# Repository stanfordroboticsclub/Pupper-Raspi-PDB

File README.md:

# Pupper Power Distribution Board for Raspberry Pi
This is a custom power distribution board for the versions of Pupper that generate PWM signals from the Raspberry Pi. 

Don't know what Pupper is? It's a cheap dynamics quadruped robot that you can build at home.
- Check out the [Project Page](https://stanfordstudentrobotics.org/pupper)
- Check out the [Code](https://github.com/stanfordroboticsclub/stanfordquadruped)

## Fabrication
1. Upload Gerbers.zip (in this directory) to the quoting mechanism on jlcpcb.com
2. It'll then give you some options on how you want the pcb made
3. Make sure you specify 2oz copper to support the high current from the servos.
4. You can leave everything else as default!

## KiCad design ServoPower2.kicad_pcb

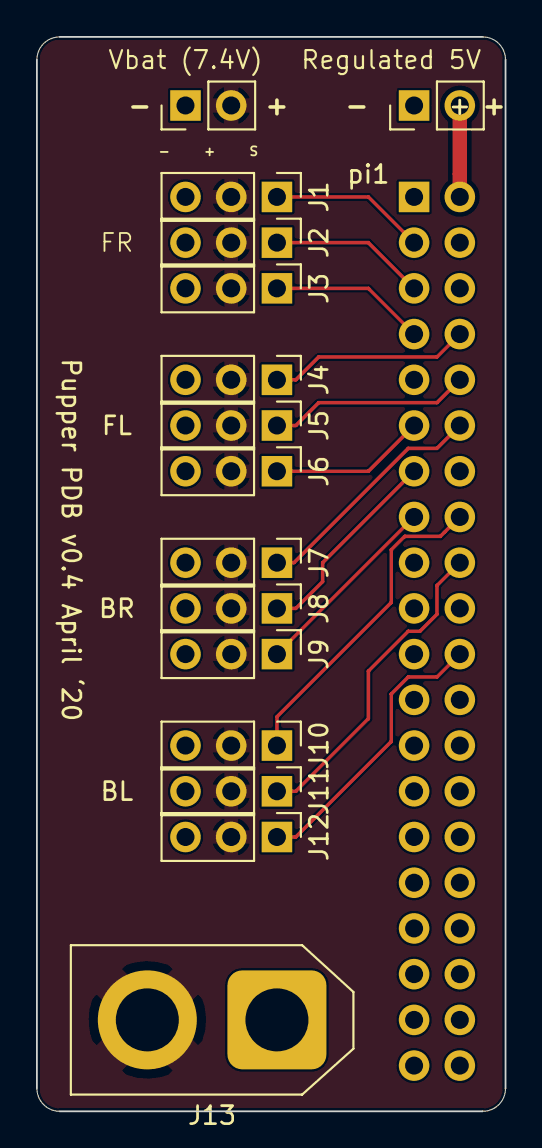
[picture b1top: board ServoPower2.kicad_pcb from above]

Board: 2 copper layers, 26.0 x 59.7 mm, 16 parts (1 on the bottom side), 15 nets.

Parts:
J1, J2, J3, J4, J5, J6, J7, J8, J9, J10, J11, J12: Conn_01x03; PinHeader_1x03_P2.54mm_Vertical
J13: Conn_01x02; AMASS_XT60-M_1x02_P7.20mm_Vertical
J14, J15: Conn_01x02; PinHeader_1x02_P2.54mm_Vertical
pi1: pi; PinSocket_2x20_P2.54mm_Vertical

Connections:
+5V: J15.2, pi1.2
/S11: J1.1, pi1.3
/S12: J2.1, pi1.5
/S13: J3.1, pi1.7
/S21: J4.1, pi1.8
/S22: J5.1, pi1.10
/S23: J6.1, pi1.11
/S31: J7.1, pi1.12
/S32: J8.1, pi1.13
/S33: J9.1, pi1.15
/S41: J10.1, pi1.16
/S42: J11.1, pi1.18
/S43: J12.1, pi1.22
GND: J1.3, J2.3, J3.3, J4.3, J5.3, J6.3, J7.3, J8.3, J9.3, J10.3, J11.3, J12.3, J13.1, J14.1, J15.1, pi1.6, pi1.9, pi1.14, pi1.20, pi1.25, pi1.30, pi1.34, pi1.39
VDD: J1.2, J2.2, J3.2, J4.2, J5.2, J6.2, J7.2, J8.2, J9.2, J10.2, J11.2, J12.2, J13.2, J14.2

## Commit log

2020-04-05 rearrange pins to easier soldering
2020-04-05 fix incomplete track
2020-04-05 update gerber zip
2020-04-22 updated spacing
2020-04-22 add readme
2020-04-22 Add project links
2020-05-01 made xt60 holes smaller to better fit 16 gauge wire rather than xt60 connector
